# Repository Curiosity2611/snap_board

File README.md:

## About the project

### Problem

Recently I came accross the ST's line of Microprocessors and I felt it fascinating. I personally felt this is one of the best Microprocessor out there in the market as it is the combination of an MPU and an  MCU. This combination has many use cases and I felt I should try this out. So I bought STM32MP157C-DK2 development board and started experimenting! <br>

Previously I had little experience working on couple of popular linux dev boards like the BeagleBone Black
and the Raspberry Pi. They are both fantastic boards to work with and they both have good community support. But while working with them, I realised a few bunch of problems:

- **Raspberry Pi Compute Module 4 + IO Board**
    - CM4 is easy to use but not ideal for mass production.
    - No support for analog signals at hardware level.
    - Software PWM possible but not very precise.
    - Cannot support real time application or processing.
    - Not fully open-source and very minimum customization possible. <br>
<br>

- **BeagleBone Black**
    - Easy to use but user has to own build hardware for production.
    - PRUs make RT applications possible but super difficult to use.
    - Cannot support MIPI-DSI and HD graphics.
    - Programming PRUs is not an easy task.

### Solution

**Best of both worlds**

**Hello World STM32MP1 !!**

- Board design inspired from Raspberry Pi Compute Module 4 and CM4 IO board.
- Operating system derived from Beaglebone Black with implementation of Bonescript Library and Cloud9 IDE.
- Footprint compatible Single or dual Cortex-A7 Processors + dedicated Cortex-M4 core for real-time and low-power applications.
- Support for MIPI-DSI display for HMI applications.
- Fully open-source Hardware and Software.

## Full Documentation

The full documentation is done using mkdocs tool and is present in the documentation folder. To view the doucmentation:
- Install mkdocs tool in your system.
- `cd` to `documentation/snap_board`
- run the command `mkdocs serve`
- Redirect your browser to `http://127.0.0.1:8000/`

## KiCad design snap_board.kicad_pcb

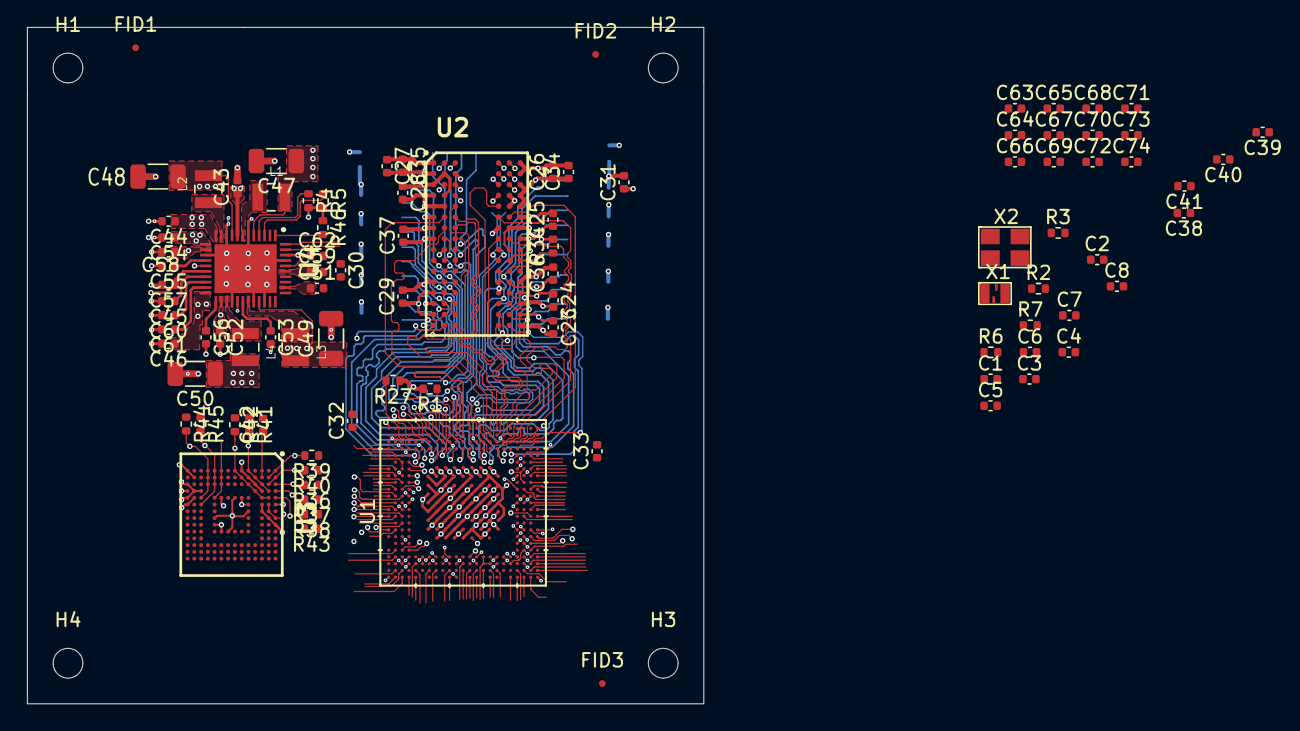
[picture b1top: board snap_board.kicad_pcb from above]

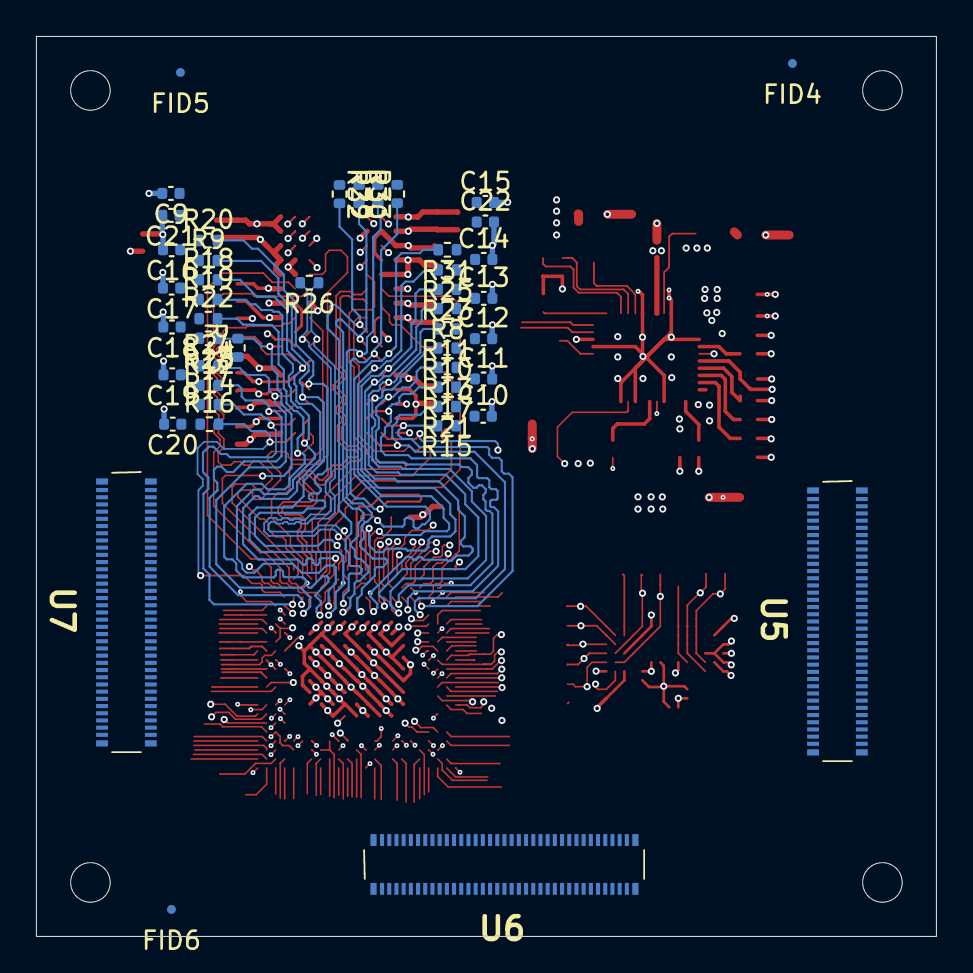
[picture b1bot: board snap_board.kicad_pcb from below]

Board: 6 copper layers, 50.0 x 50.0 mm, 143 parts (46 on the bottom side), 97 nets.

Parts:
C1, C2, C5, C6, C51, C52, C63, C64, C65, C66, C67, C68, C69, C70, C71, C72, C73, C74: 1uF; C_0402_1005Metric
C3, C4, C8, C9, C10, C11, C12, C13, C14, C15, C16, C17, C18, C19, C20, C23, C24, C25, C26, C27, C28, C29, C30, C31, C32, C33, C36, C37, C38, C39, C40: 100nF; C_0402_1005Metric
C7: 10nF; C_0402_1005Metric
C21, C22, C34, C35, C41, C43, C44, C45, C46, C54: 10uF; C_0402_1005Metric
C42: 2.2uF; C_0402_1005Metric
C47, C48, C49, C50: 22uF; C_1206_3216Metric
C53, C55, C56, C57, C58, C59, C60, C61, C62: 4.7uF; C_0402_1005Metric
FID1, FID2, FID3, FID4, FID5, FID6: Fiducial; Fiducial_0.5mm_Mask1.5mm
H1, H2, H3, H4: MountingHole_Pad; MountingHole_2.2mm_M2
L1, L2, L3, L4: 1uH; MGV2520101R0M-10
R1, R34: 240E; R_0402_1005Metric
R2, R3, R4, R5: 1k5; R_0402_1005Metric
R6, R27, R35, R46: 10k; R_0402_1005Metric
R7: 3k; R_0402_1005Metric
R8, R9, R10, R11, R12, R13, R14, R15, R16, R17, R18, R19, R20, R21, R22, R23, R24, R25, R28, R29, R30, R31, R32, R33: 56E; R_0402_1005Metric
R26: 100E; R_0402_1005Metric
R36, R37, R38, R39, R40, R41, R42, R43, R44, R45: 47k; R_0402_1005Metric
U1: STM32MP157CAC3
U2: AS4C256M16D3LC-12BCN
U3: S40FC004C1B2C00000
U4: STPMIC1BPQR
U5, U6, U7: DF40C-70DP-0.4V(51); DF40C70DP04V51
X1: 32.768kHz; SiT1533AC-H5-DCC-32.768E
X2: 24MHz; TSX3225240000MF10ZC3

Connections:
5V_VIN: C43.1, C44.1, C45.1, C46.1, C51.1, C52.1, C53.1, U4.8, U4.12, U4.19, U4.22, U4.24, U4.28, U4.36
DDR_A0: R8.2, U1.L20, U2.N3
DDR_A1: R9.2, U1.P22, U2.P7
DDR_A2: R10.2, U1.J20, U2.P3
DDR_A3: R11.2, U1.K22, U2.N2
DDR_A4: R12.2, U1.V20, U2.P8
DDR_A5: R13.2, U1.H20, U2.P2
DDR_A6: R14.2, U1.W20, U2.R8
DDR_A7: R15.2, U1.E20, U2.R2
DDR_A8: R16.2, U1.Y20, U2.T8
DDR_A9: R17.2, U1.G20, U2.R3
DDR_A10: R18.2, U1.R22, U2.L7
DDR_A11: R19.2, U1.R20, U2.R7
DDR_A12: R20.2, U1.P23, U2.N7
DDR_A13: R21.2, U1.F20, U2.T3
DDR_A14: R22.2, U1.R21, U2.T7
DDR_BA0: R23.2, U1.L23, U2.M2
DDR_BA1: R24.2, U1.U20, U2.N8
DDR_BA2: R25.2, U1.M21, U2.M3
DDR_CASN: R33.2, U1.N20, U2.K3
DDR_CKE: R28.1, R35.2, U1.T20, U2.K9
DDR_CLK_N: R26.1, U1.N23, U2.K7
DDR_CLK_P: R26.2, U1.N22, U2.J7
DDR_CSN: R30.1, U1.M22, U2.L2
DDR_DQ0: U1.E22, U2.A2
DDR_DQ1: U1.F22, U2.C3
DDR_DQ2: U1.H21, U2.A7
DDR_DQ3: U1.E21, U2.C2
DDR_DQ4: U1.J21, U2.B8
DDR_DQ5: U1.J22, U2.C8
DDR_DQ6: U1.H22, U2.D7
DDR_DQ7: U1.G21, U2.A3
DDR_DQ8: U1.T21, U2.F2
DDR_DQ9: U1.U21, U2.E3
DDR_DQ10: U1.T22, U2.G2
DDR_DQ11: U1.W21, U2.F7
DDR_DQ12: U1.W23, U2.H8
DDR_DQ13: U1.T23, U2.H3
DDR_DQ14: U1.W22, U2.H7
DDR_DQ15: U1.Y21, U2.F8
DDR_DQM0: U1.H23, U2.D3
DDR_DQM1: U1.V22, U2.E7
DDR_DQS0_N: U1.G23, U2.B7
DDR_DQS0_P: U1.G22, U2.C7
DDR_DQS1_N: U1.U23, U2.G3
DDR_DQS1_P: U1.U22, U2.F3
DDR_ODT: R31.2, U1.L22, U2.K1
DDR_RASN: R29.2, U1.N21, U2.J3
DDR_RESETN: R27.2, U1.D20, U2.T2
DDR_WEN: R32.1, U1.M20, U2.L3
ETH_NRST: R6.1, U1.AC2
GND: C1.2, C2.2, C3.2, C4.2, C5.1, C6.2, C7.2, C8.2, C9.2, C10.2, C11.2, C12.2, C13.2, C14.2, C15.2, C16.2, C17.2, C18.2, C19.2, C20.2, C21.2, C22.2, C23.2, C24.2, C25.2, C26.2, C27.2, C28.2, C29.2, C30.2, C31.2, C32.2, C33.2, C34.2, C35.2, C36.2, C37.2, C38.2, C39.2, C40.2, C41.2, C42.2, C43.2, C44.2, C45.2, C46.2, C47.2, C48.2, C49.2, C50.2, C51.2, C52.2, C53.2, C54.2, C55.2, C56.2, C57.2, C58.2, C59.2, C60.2, C61.2, C62.2, C63.2, C64.2, C65.2, C66.2, C67.2, C68.2, C69.2, C70.2, C71.2, C72.2, C73.2, C74.2, R1.2, R7.2, R27.1, R34.2, R35.1, U1.1A3, U1.1A5, U1.1A7, U1.1B2, U1.1B4, U1.1B6, U1.1B8, U1.1C1, U1.1C3, U1.1C5, U1.1C7, U1.1C9, U1.1D2, U1.1D4, U1.1D6, U1.1D8, U1.1E1, U1.1E3, U1.1E5, U1.1E7, U1.1E9, U1.1F2, U1.1F4, U1.1F6, U1.1F8, U1.1G1, U1.1G3, U1.1G5, U1.1G7, U1.1G9, U1.1H2, U1.1H4, U1.1H6, U1.1H8, U1.1J3, U1.1J5, U1.1J7, U1.A1, U1.A23, U1.AA5, U1.AA8, U1.AA12, U1.AA16, U1.AA21, U1.AB13, U1.AC1, U1.AC23, U1.C7, U1.C12, U1.C16, U1.C21, U1.D4, U1.F21, U1.H3, U1.K21, U1.L1, U1.P3, U1.P21, U1.V21, U1.W3, U2.A9, U2.B1, U2.B3, U2.B9, U2.D1, U2.D8, U2.E1, U2.E2, U2.E8, U2.F9, U2.G1, U2.G8, U2.G9, U2.J2, U2.J8, U2.M1, U2.M9, U2.P1, U2.P9, U2.T1, U2.T9, U3.A6, U3.C4, U3.D3, U3.E2, U3.E7, U3.F1, U3.G5, U3.H10, U3.J5, U3.K8, U3.N2, U3.N5, U3.P1, U3.P4, U3.P6, U4.6, U4.10, U4.15, U4.26, U4.30, U4.32, U4.41, U4.ep, X1.2, X2.2, X2.4
I2C1_SCL: R2.1, U1.Y18
I2C1_SDA: R3.1, U1.Y4
I2C4_SCL: R4.1, U1.G2, U4.4
I2C4_SDA: R5.1, U1.H2, U4.3
MPU_VDDA_1V8_REG: C1.1, C4.1, U1.AB14, U1.C14
NRST: R46.2, U1.M3, U3.J1, U3.J2, U3.J3, U3.K5, U4.1
unnamed: C5.2, U1.C17, U1.C18
unnamed: C6.1, U1.AB15
unnamed: C7.1, U1.M4
unnamed: C42.1, U3.C1, U3.C2
unnamed: C62.1, U4.40
unnamed: L1.1, U4.7
unnamed: L2.1, U4.11
unnamed: L3.1, U4.29
unnamed: L4.1, U4.25
unnamed: R1.1, U1.K23
unnamed: R7.1, U1.AB18
unnamed: R34.1, U2.L8
unnamed: U1.L2, X1.3
unnamed: U1.P1, X2.1
unnamed: U1.P2, X2.3
PA0_WKUP: U1.AB3, U4.43
PMIC_LDO1_1V8: C56.1, U4.23
PMIC_LDO2_2V9: C57.1, U4.18
PMIC_LDO3_VTT_DDR: C9.1, C10.1, C11.1, C12.1, C13.1, C14.1, C15.1, C16.1, C17.1, C18.1, C19.1, C20.1, C21.1, C22.1, C58.1, R8.1, R9.1, R10.1, R11.1, R12.1, R13.1, R14.1, R15.1, R16.1, R17.1, R18.1, R19.1, R20.1, R21.1, R22.1, R23.1, R24.1, R25.1, R28.2, R29.1, R30.2, R31.1, R32.2, R33.1, U4.14
PMIC_LDO4_VDD_USB: C3.1, C59.1, U1.AA15, U1.AA17, U4.39
PMIC_LDO5: C60.1, U4.20
PMIC_LDO6_1V0: C61.1, U4.21
PMIC_VOUT1_VDD_CORE: C47.1, C63.1, C64.1, C65.1, C66.1, L1.2, U1.1A2, U1.1A4, U1.1A6, U1.1B1, U1.1B3, U1.1B5, U1.1C2, U1.1C4, U1.1C6, U1.1D1, U1.1D3, U1.1D5, U1.1D7, U1.1E2, U1.1E4, U1.1E6, U1.1F5, U1.1F7, U1.1G6, U1.1H7, U4.5
PMIC_VOUT2_VDD_DDR: C23.1, C24.1, C25.1, C26.1, C27.1, C28.1, C29.1, C30.1, C31.1, C32.1, C33.1, C34.1, C35.1, C48.1, C54.1, C71.1, C72.1, C73.1, C74.1, L2.2, U1.1A8, U1.1B7, U1.1B9, U1.1C8, U1.1D9, U1.1E8, U1.1F9, U1.1G8, U1.1H9, U1.1J8, U2.A1, U2.A8, U2.B2, U2.C1, U2.C9, U2.D2, U2.D9, U2.E9, U2.F1, U2.G7, U2.H2, U2.H9, U2.K2, U2.K8, U2.N1, U2.N9, U2.R1, U2.R9, U4.9, U4.13
PMIC_VOUT3_VDD: C2.1, C38.1, C39.1, C40.1, C41.1, C49.1, C67.1, C68.1, C69.1, C70.1, L3.2, R2.2, R3.2, R4.2, R5.2, R6.2, R36.1, R37.1, R38.1, R39.1, R40.1, R41.1, R42.1, R43.1, R44.1, R45.1, R46.1, U1.1F1, U1.1F3, U1.1G2, U1.1G4, U1.1H1, U1.1H3, U1.1H5, U1.1J2, U1.1J4, U1.1J6, U1.B18, U1.R3, U1.R4, U1.T3, U3.A9, U3.B8, U3.C6, U3.C7, U3.E6, U3.F5, U3.J10, U3.K9, U3.M4, U3.N4, U3.P3, U3.P5, U4.31, U4.42, X1.4
PMIC_VOUT4_3V3: C50.1, L4.2, U4.27
PMIC_VREF_DDR: C8.1, C36.1, C37.1, C55.1, U1.AC20, U2.H1, U2.M8, U4.16
PMIC_WAKEUP: U1.K2, U4.2
POWER_ON: U1.R2, U4.44
SDMMC2_CK: R45.2, U1.C9, U3.K1, U3.K2, U3.K3, U3.M6
SDMMC2_CMD: R44.2, U1.A10, U3.L1, U3.L2, U3.L3, U3.M5
SDMMC2_D0: R36.2, U1.C13, U3.A3
SDMMC2_D1: R37.2, U1.B12, U3.A4
SDMMC2_D2: R38.2, U1.A11, U3.A5
SDMMC2_D3: R39.2, U1.B13, U3.A1, U3.B2
SDMMC2_D4: R40.2, U1.AB10, U3.A2, U3.B3
SDMMC2_D5: R41.2, U1.A8, U3.B4, U3.C3, U3.D2, U3.E1
SDMMC2_D6: R42.2, U1.C11, U3.B5, U3.C5, U3.D4, U3.E3, U3.F2, U3.G1
SDMMC2_D7: R43.2, U1.B11, U3.A8, U3.B6, U3.B7

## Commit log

2021-05-20 Added README file
2021-05-20 Added Project Overview Block Diagram
2021-05-20 Small changes
2021-05-21 working on pmic
2021-05-21 completed PMIC
2021-05-21 added notes to pmic
2021-05-21 working on mpu power
2021-05-21 MPU power complete
2021-05-22 working on mpu
2021-05-22 MPU_1 completed
2021-05-22 working on RAM
2021-05-22 working on DDR
2021-05-22 minor mods on ram
2021-05-22 minor mods
2021-05-22 working on emmc
2021-05-23 ref designators
2021-05-23 added design documentation
2021-05-23 updated documentation
2021-05-23 updated readme file
2021-05-23 removed unwanted files
2021-05-23 removed notes
2021-05-23 removed waste files
2021-05-23 edited readme file
2021-05-23 modified documentation
2021-05-23 modifications
2021-05-23 documentation update
2021-05-23 sch mods
2021-05-24 sch changes
2021-05-24 added footprints
2021-05-24 corrected symbol
2021-05-24 updated stm32 footprint
2021-05-24 working on bga fanout
2021-05-25 working on PCB
2021-05-26 still working on RAM
2021-05-27 ram almost complete
2021-05-27 ram complete
2021-05-28 modified sch and layout

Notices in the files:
parts and their libraries:
Copyright 2016 Accelerated Designs. All rights reserved.
